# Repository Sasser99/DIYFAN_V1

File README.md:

# DIY-Fan-V1

Files from the YouTube video: **"DIY Fan V1 – I Built This Modular Open Source Project"**

https://www.youtube.com/watch?v=IbPePFFd2lk

## Project structure

- **ECAD/** – KiCad files  
- **CODE/** – Arduino code  
- **CAD/** – 3D models (STL, STEP)
- **BOM/** – Each assembly has its own BOM, organized in separate worksheets within a single .ods file.

## License

This project is open source and licensed as follows:

- **ECAD:** CERN Open Hardware License v2.0  
- **CODE:** MIT License  
- **CAD:** Creative Commons Attribution 4.0 (CC BY 4.0)

➡️ For full license texts, see the [LICENSE](LICENSE) file.

## Story

I came up with the idea to develop a modular, battery-powered, open-source fan built around high-end gaming PC fans. Gaming PC fans have low power consumption and, in the best case, are very quiet. Both are qualities that are also useful when the goal is not to cool PC components, but people. Additionally, the goal was to create a visually appealing and functional design.

The result is a system with **three main assemblies**: 

### 1. Fan Stage

- This assembly consists of three parts: a fan, the interface_V1 PCBA, and the shroud.
- I chose the **Noctua NF-A12x25 PWM chromax.black.swap**, which offers a solid balance between airflow and static pressure.
- Other fans can be used as long as they have similar characteristics (e.g., airflow and static pressure).
- The shroud **increases wind speed by around 80%**, allowing the fan to be placed further away while still being effective. More on this in the YouTube video! :)
- The interface_V1 PCBA is mounted on the side and connects to the fan, forwarding its signals.

### 2. Main Electronics Module

- This module supplies approximately **10W** of power. With fans like the Noctua NF-A12x25, up to five fan stages can be powered simultaneously.
- A single **button** is used to cycle through PWM levels.
- Four **RGB LEDs**, visible through the plexiglass cover, indicate the active PWM level.

- I chose the **Arduino Nano** because it's compact, easy to use via the Arduino IDE, and perfect for replicating the build—especially for those with Arduino experience.
- The Nano is mounted on a small **custom PCB** that also houses LEDs, DC-DC converters, and a few additional components. But don’t worry: the total component count remains very manageable.
- I also used a **15W power bank** instead of a custom battery to keep replication easy.

### 3. Tripod

- The tripod is simple but functional. If the legs are cut cleanly, the fan stands level.
- It provides the necessary stability, and I think the wood finish enhances the overall aesthetic.

### Configurations

The overall goal was to create a modular system. The three assemblies can be combined in different configurations using mechanical connectors and standard **Ethernet cables**, which transmit both power and PWM signal. The following configurations are demonstrated in the YouTube video:

**Full Build (with 3/5 Fans)**

**Desk Setup**

**Split Mode (Left and Right → Stereo)**

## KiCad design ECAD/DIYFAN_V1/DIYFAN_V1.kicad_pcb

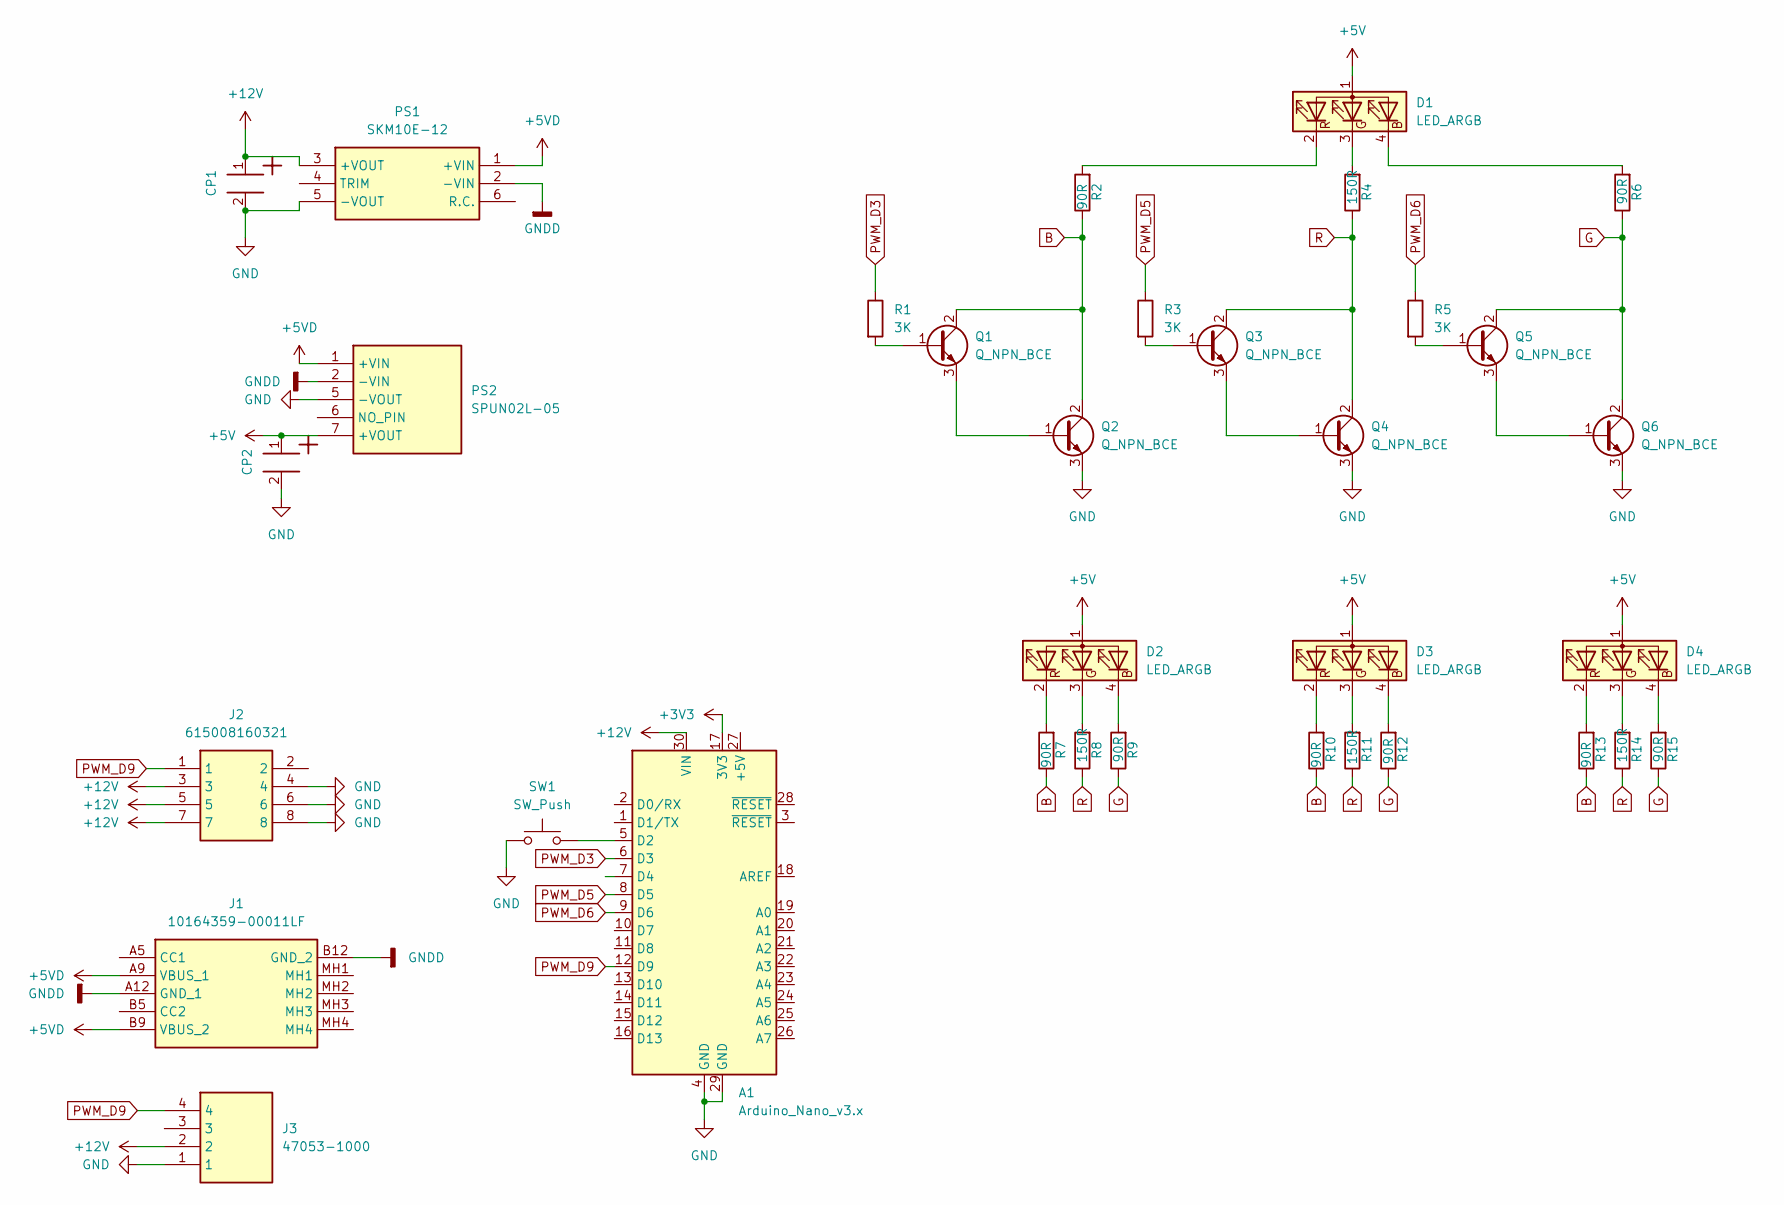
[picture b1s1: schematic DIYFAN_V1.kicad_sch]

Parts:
A1: Arduino_Nano_v3.x; Arduino_Nano
CP1, CP2: P2.5D6.3L11_860010573007_Modified; CP_Wurth_WCAP-ATG8-P2.5D6.3L11; Part Number 860010573007
D1, D2, D3, D4: LED_ARGB; 150141M173100
J1: 10164359-00011LF; 1016435900011LF_handsoldered; Mouser Part Number 649-10164359-00011LF
J2: 615008160321; Mouser Part Number 710-615008160321
J3: 47053-1000; 470531000; Mouser Part Number 538-47053-1000
PS1: SKM10E-12; SKM10B05; Mouser Part Number 709-SKM10E-12
PS2: SPUN02L-05; SPUN02L05; Mouser Part Number 709-SPUN02L-05
Q1, Q2, Q3, Q4, Q5, Q6: Q_NPN_BCE; SOT-23-3
R1, R3, R5: 3K; R_1206_3216Metric_Pad1.30x1.75mm_HandSolder
R2, R6, R7, R9, R10, R12, R13, R15: 90R; R_1206_3216Metric_Pad1.30x1.75mm_HandSolder
R4, R8, R11, R14: 150R; R_1206_3216Metric_Pad1.30x1.75mm_HandSolder
SW1: SW_Push; SW_PUSH_6mm_H13mm

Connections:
+3V3: A1.17 (3V3)
+5V: CP2.1, D1.1 (A), D2.1 (A), D3.1 (A), D4.1 (A), PS2.7 (+VOUT)
+5VD: J1.A9 (VBUS_1), J1.B9 (VBUS_2), PS1.1 (+VIN), PS2.1 (+VIN)
+12V: A1.30 (VIN), CP1.1, J2.3, J2.5, J2.7, J3.2, PS1.3 (+VOUT)
B: Q1.2 (C), Q2.2 (C), R2.1, R7.1, R10.1, R13.1
G: Q5.2 (C), Q6.2 (C), R6.1, R9.1, R12.1, R15.1
GND: A1.4 (GND), A1.29 (GND), CP1.2, CP2.2, J2.4, J2.6, J2.8, J3.1, PS1.5 (-VOUT), PS2.5 (-VOUT), Q2.3 (E), Q4.3 (E), Q6.3 (E), SW1.1
GNDD: J1.A12 (GND_1), J1.B12 (GND_2), PS1.2 (-VIN), PS2.2 (-VIN)
unnamed: A1.5 (D2), SW1.2
unnamed: D1.4 (BK), R6.2
unnamed: D1.3 (GK), R4.2
unnamed: D1.2 (RK), R2.2
unnamed: D2.4 (BK), R9.2
unnamed: D2.3 (GK), R8.2
unnamed: D2.2 (RK), R7.2
unnamed: D3.4 (BK), R12.2
unnamed: D3.3 (GK), R11.2
unnamed: D3.2 (RK), R10.2
unnamed: D4.4 (BK), R15.2
unnamed: D4.3 (GK), R14.2
unnamed: D4.2 (RK), R13.2
unnamed: Q1.1 (B), R1.2
unnamed: Q1.3 (E), Q2.1 (B)
unnamed: Q3.1 (B), R3.2
unnamed: Q3.3 (E), Q4.1 (B)
unnamed: Q5.1 (B), R5.2
unnamed: Q5.3 (E), Q6.1 (B)
PWM_D3: A1.6 (D3), R1.1
PWM_D5: A1.8 (D5), R3.1
PWM_D6: A1.9 (D6), R5.1
PWM_D9: A1.12 (D9), J2.1, J3.4
R: Q3.2 (C), Q4.2 (C), R4.1, R8.1, R11.1, R14.1

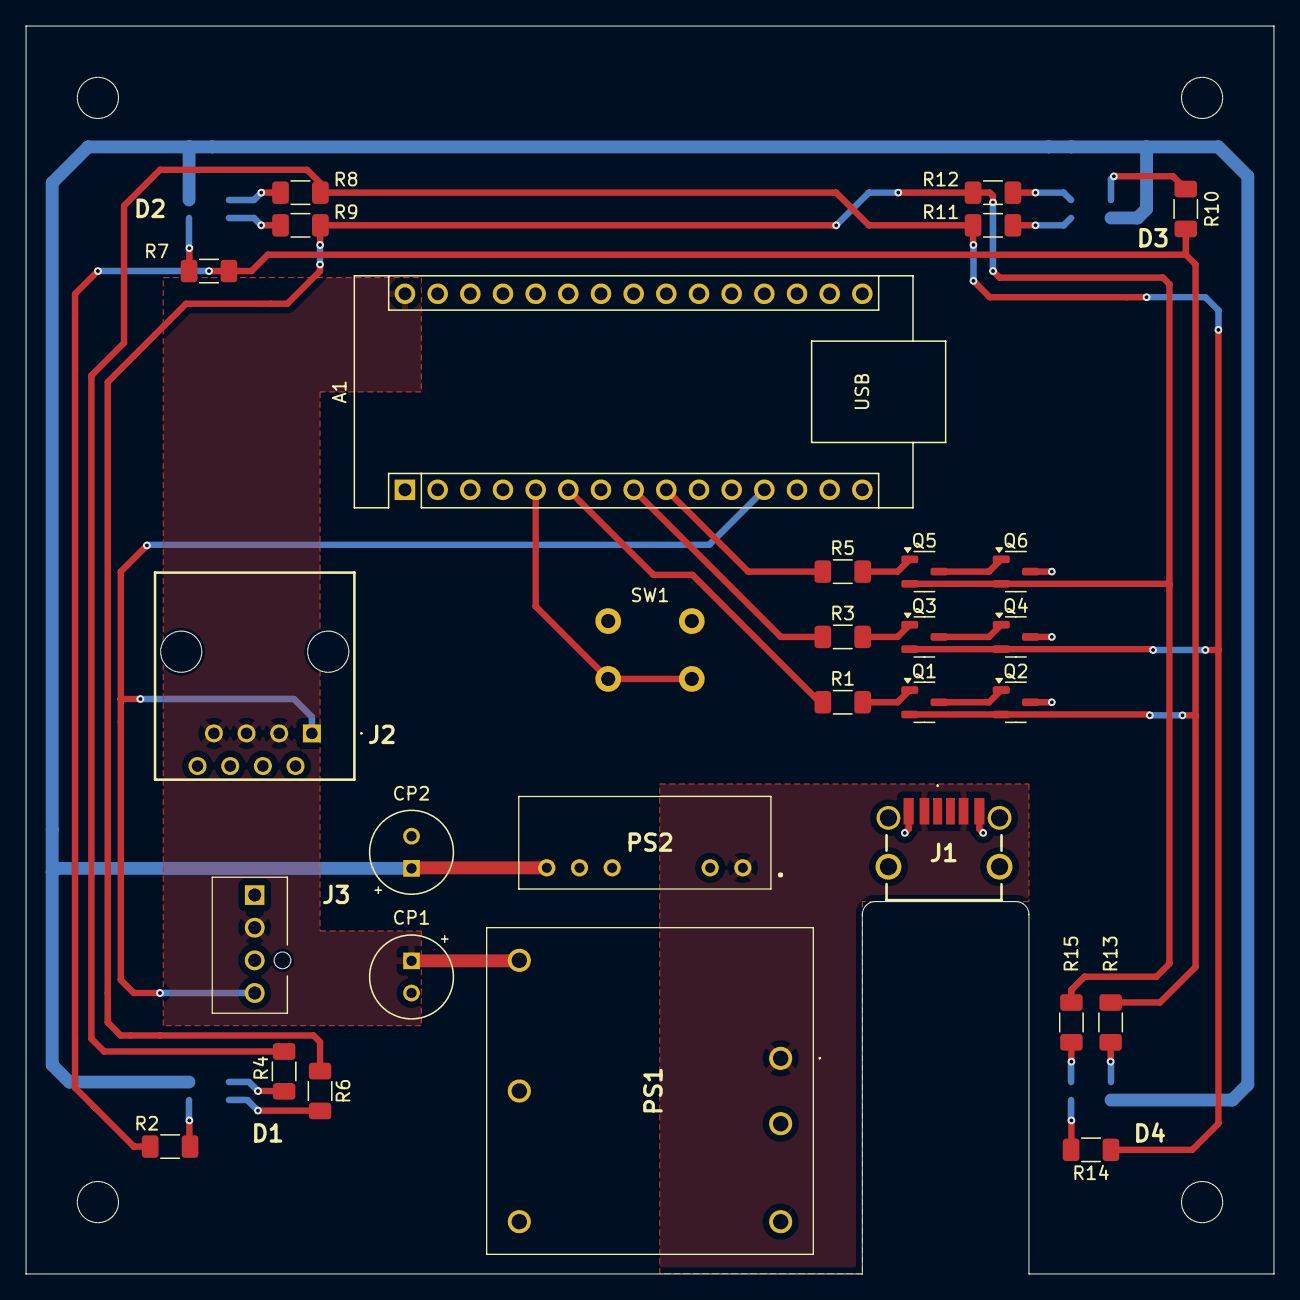
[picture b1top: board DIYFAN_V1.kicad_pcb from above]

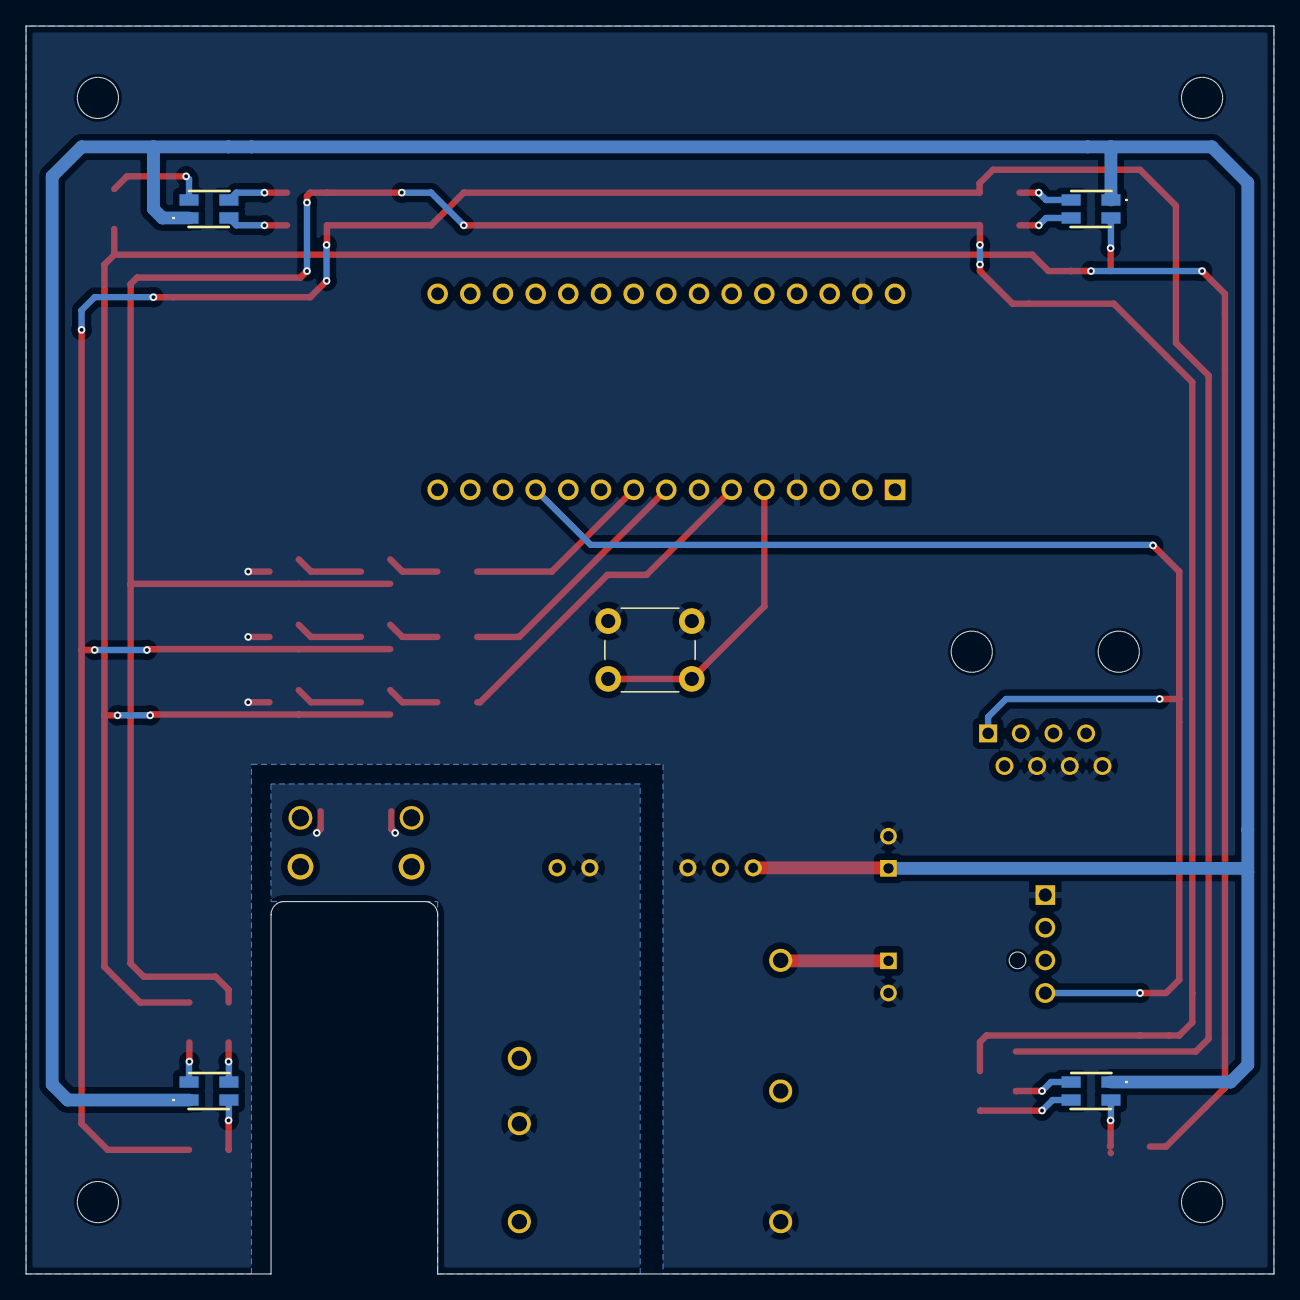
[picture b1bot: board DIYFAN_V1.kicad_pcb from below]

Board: 2 copper layers, 97.0 x 97.0 mm, 34 parts (5 on the bottom side), 31 nets.

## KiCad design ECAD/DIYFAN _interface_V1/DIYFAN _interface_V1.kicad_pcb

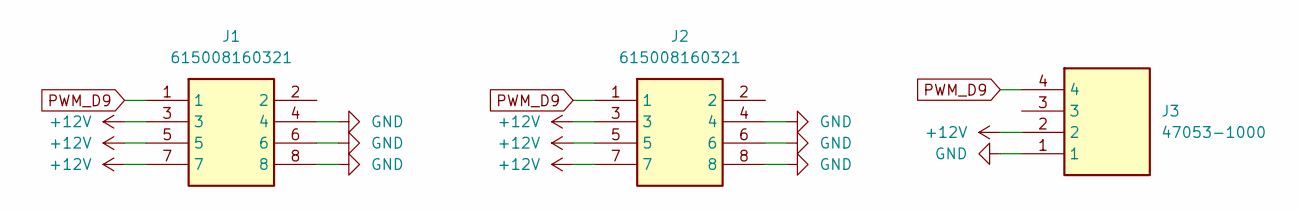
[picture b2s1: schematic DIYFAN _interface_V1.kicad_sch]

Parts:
J1, J2: 615008160321; Mouser Part Number 710-615008160321
J3: 47053-1000; 470531000; Mouser Part Number 538-47053-1000

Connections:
+12V: J1.3, J1.5, J1.7, J2.3, J2.5, J2.7, J3.2
GND: J1.4, J1.6, J1.8, J2.4, J2.6, J2.8, J3.1
PWM_D9: J1.1, J2.1, J3.4

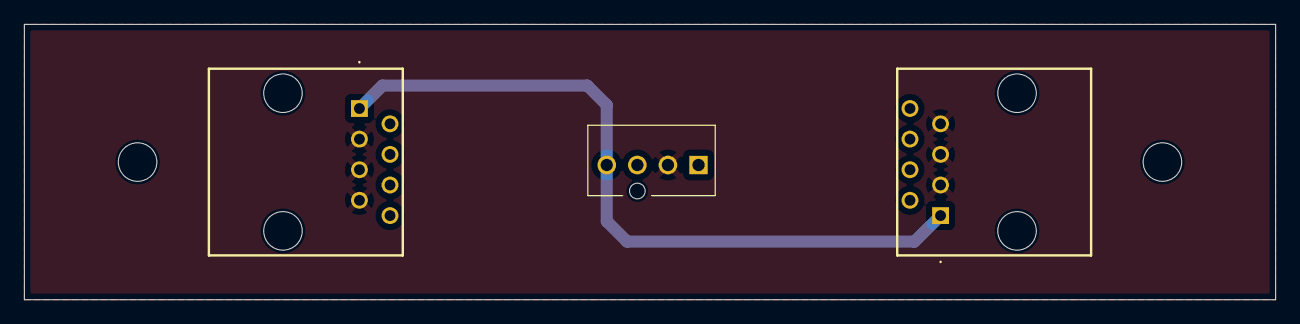
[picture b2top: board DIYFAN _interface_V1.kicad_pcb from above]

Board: 2 copper layers, 103.9 x 22.9 mm, 3 parts (0 on the bottom side), 3 nets.

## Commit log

2025-06-02 some modifications
2025-06-02 further changes
2025-06-02 added Hardware Architecture png
2025-06-02 deleted tmp file
2025-06-02 modified README
2025-06-02 added csv BOMs
2025-06-02 added story
2025-06-03 ready for YouTube
2025-06-03 modified story
2025-06-03 modified story again
2025-06-03 modified img
2025-06-03 modiefied readme again
2025-06-03 added youtube url
2025-06-04 modiefied rdm
2025-06-04 changed thumbnail
2025-06-04 added thumbnail change in rdm
2025-06-06 changed thumbnail again
2025-06-06 modiefied readme
2025-06-06 changed readme
2025-06-06 changed BOM
2025-06-08 added picture
2025-06-08 modified readme again
2025-06-15 added further informations
2025-06-15 almost finished
2025-06-15 ready for first release
2025-06-15 a few changes
2025-06-16 ready
